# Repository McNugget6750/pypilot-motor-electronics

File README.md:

# pypilot-motor-electronics
Electronics for highly modified pypilot motor in my other repository

I spend the better part of a month to understand and rewrite major parts of the original pypilot motor controller code originally created by seandepagnier moderating the http://forum.openmarine.net/forumdisplay.php?fid=18 forum.

He did an amazing job pulling all these different software packages of OpenPlotter together and creating and maintaining the majority of them as far as I understand. However, the motor controller code needed some work and the controller hardware and h-bridge support needed polishing. I hope I was able to do both.

Design decisions:
* single sided
* hand assembly must be easy
* easy to understand schematics
* support for all sensors and switches originally supported by Sean's code
* additional display for debugging and state information

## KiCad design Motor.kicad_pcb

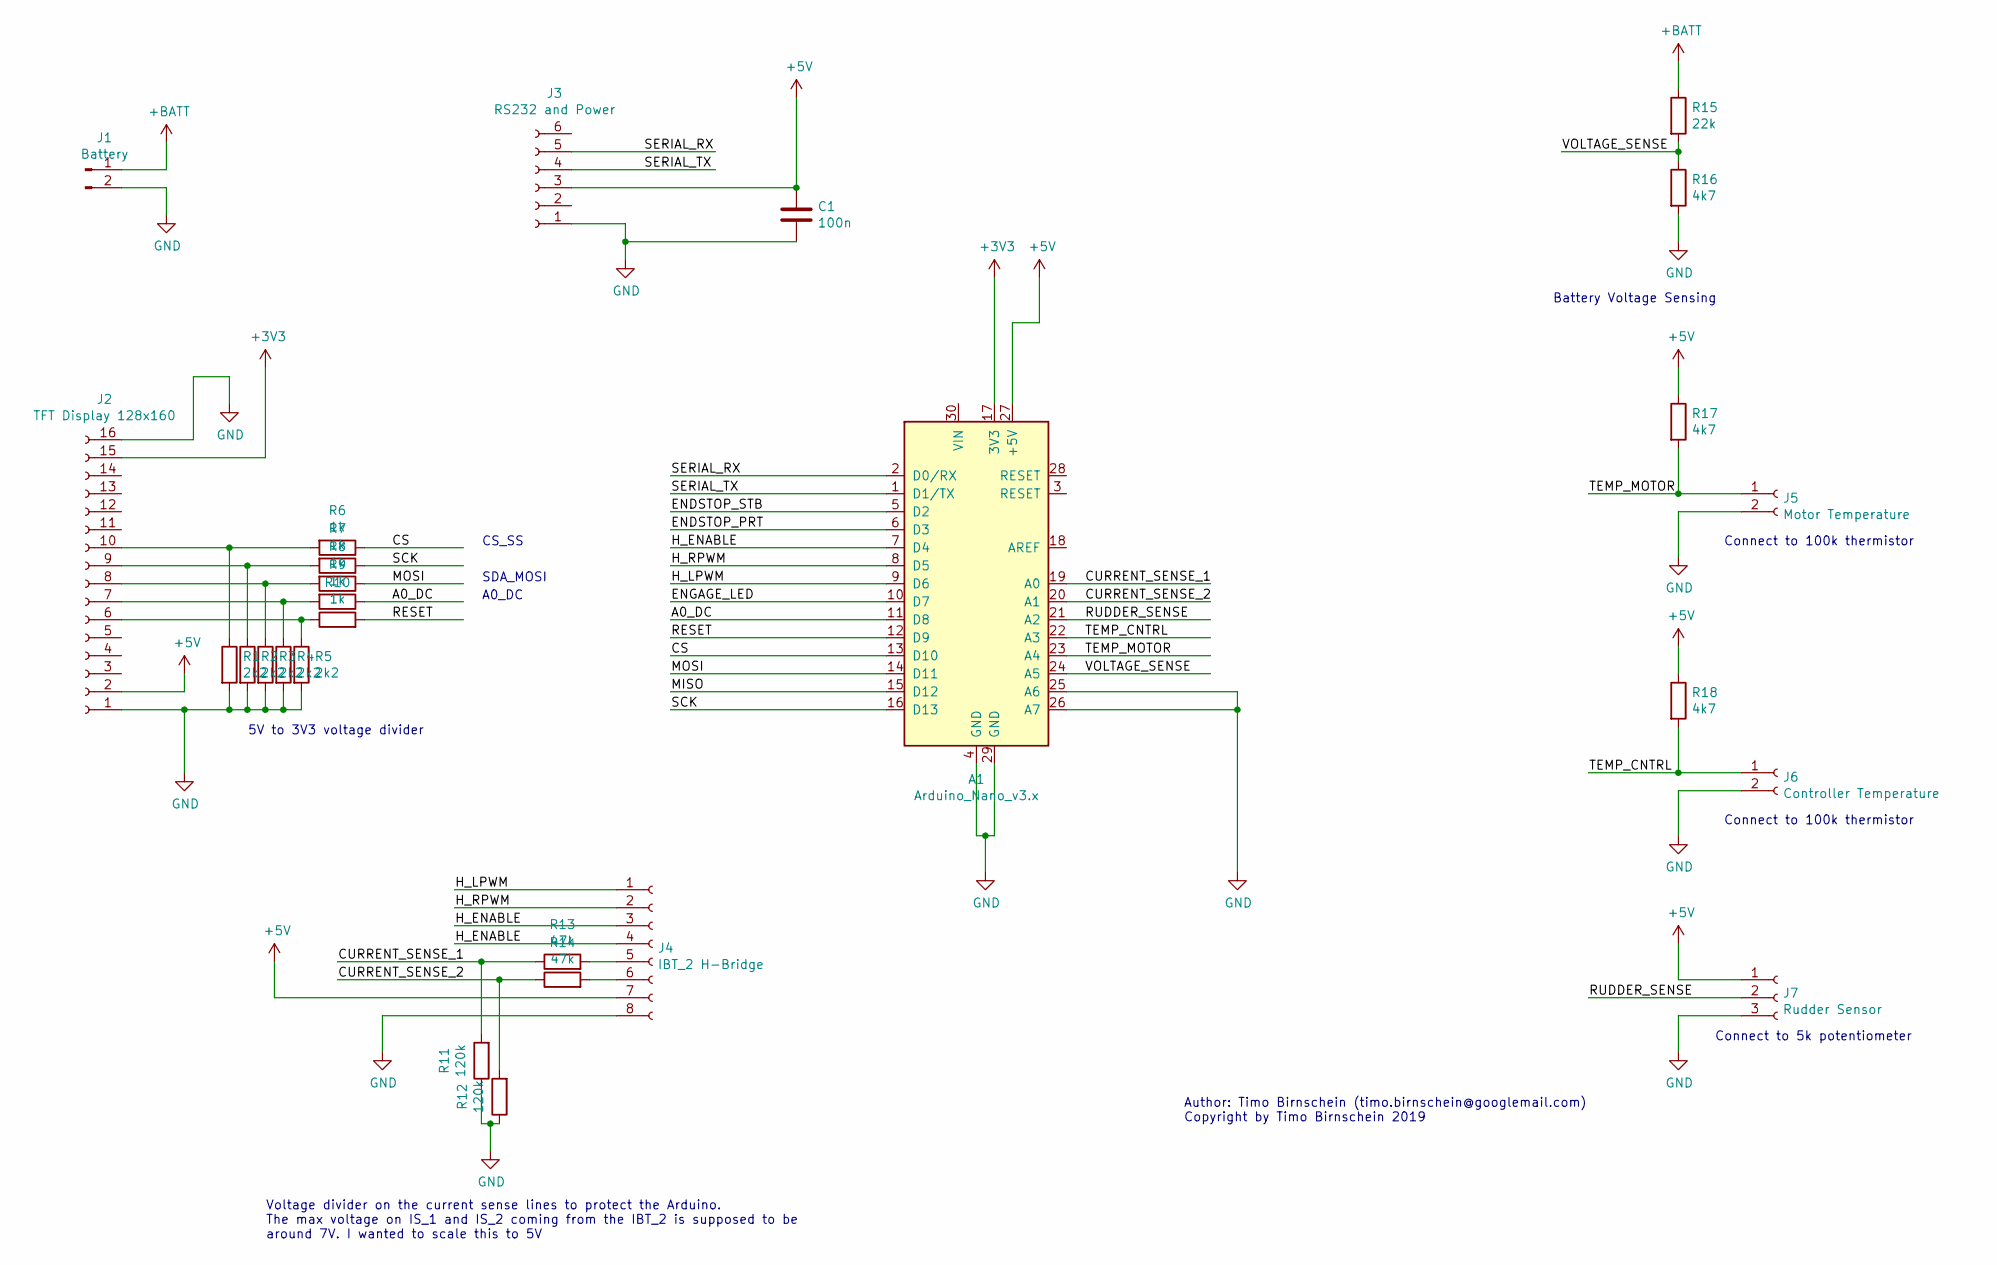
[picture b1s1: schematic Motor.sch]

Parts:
A1: Arduino_Nano_v3.x; Arduino_Nano
C1: 100n; C_0603_1608Metric_Pad1.05x0.95mm_HandSolder
J1: Battery; PinHeader_1x02_P2.54mm_Vertical
J2: TFT Display 128x160; PinHeader_1x16_P2.54mm_Vertical
J3: RS232 and Power; PinHeader_1x06_P2.54mm_Vertical
J4: IBT_2 H-Bridge; PinHeader_1x08_P2.54mm_Vertical
J5: Motor Temperature; PinHeader_1x02_P2.54mm_Vertical
J6: Controller Temperature; PinHeader_1x02_P2.54mm_Vertical
J7: Rudder Sensor; PinHeader_1x03_P2.54mm_Vertical
R1, R2, R3, R4, R5: 2k2; R_Axial_DIN0204_L3.6mm_D1.6mm_P7.62mm_Horizontal
R6, R7, R8, R9, R10: 1k; R_Axial_DIN0204_L3.6mm_D1.6mm_P7.62mm_Horizontal
R11, R12: 120k; R_Axial_DIN0204_L3.6mm_D1.6mm_P7.62mm_Horizontal
R13, R14: 47k; R_Axial_DIN0204_L3.6mm_D1.6mm_P7.62mm_Horizontal
R15: 22k; R_Axial_DIN0204_L3.6mm_D1.6mm_P7.62mm_Horizontal
R16, R17, R18: 4k7; R_Axial_DIN0204_L3.6mm_D1.6mm_P7.62mm_Horizontal

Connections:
+3V3: A1.17 (3V3), J2.15
+5V: A1.27 (+5V), C1.1, J2.2, J3.3, J4.7, J7.1, R17.1, R18.1
+BATT: J1.1, R15.1
/A0_DC: A1.11 (D8), R9.1
/CS: A1.13 (D10), R6.1
/CURRENT_SENSE_1: A1.19 (A0), R11.2, R13.1
/CURRENT_SENSE_2: A1.20 (A1), R12.2, R14.1
/ENDSTOP_PRT: A1.6 (D3)
/ENDSTOP_STB: A1.5 (D2)
/ENGAGE_LED: A1.10 (D7)
/H_ENABLE: A1.7 (D4), J4.3, J4.4
/H_LPWM: A1.9 (D6), J4.1
/H_RPWM: A1.8 (D5), J4.2
/MISO: A1.15 (D12)
/MOSI: A1.14 (D11), R8.1
/RESET: A1.12 (D9), R10.2
/RUDDER_SENSE: A1.21 (A2), J7.2
/SCK: A1.16 (D13), R7.1
/SERIAL_RX: A1.2 (D0/RX), J3.5
/SERIAL_TX: A1.1 (D1/TX), J3.4
/TEMP_CNTRL: A1.22 (A3), J6.1, R18.2
/TEMP_MOTOR: A1.23 (A4), J5.1, R17.2
/VOLTAGE_SENSE: A1.24 (A5), R15.2, R16.1
GND: A1.4 (GND), A1.25 (A6), A1.26 (A7), A1.29 (GND), C1.2, J1.2, J2.1, J2.16, J3.1, J4.8, J5.2, J6.2, J7.3, R1.2, R2.2, R3.2, R4.2, R5.2, R11.1, R12.1, R16.2
unnamed: J2.6, R5.1, R10.1
unnamed: J2.7, R4.1, R9.2
unnamed: J2.8, R3.1, R8.2
unnamed: J2.9, R2.1, R7.2
unnamed: J2.10, R1.1, R6.2
unnamed: J4.5, R13.2
unnamed: J4.6, R14.2

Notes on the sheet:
5V to 3V3 voltage divider
Battery Voltage Sensing
SDA_MOSI
CS_SS
A0_DC
Voltage divider on the current sense lines to protect the Arduino. The max voltage on IS_1 and IS_2 coming from the IBT_2 is supposed to be around 7V. I wanted to scale this to 5V
Connect to 100k thermistor
Connect to 5k potentiometer
Author: Timo Birnschein (timo.birnschein@googlemail.com) Copyright by Timo Birnschein 2019

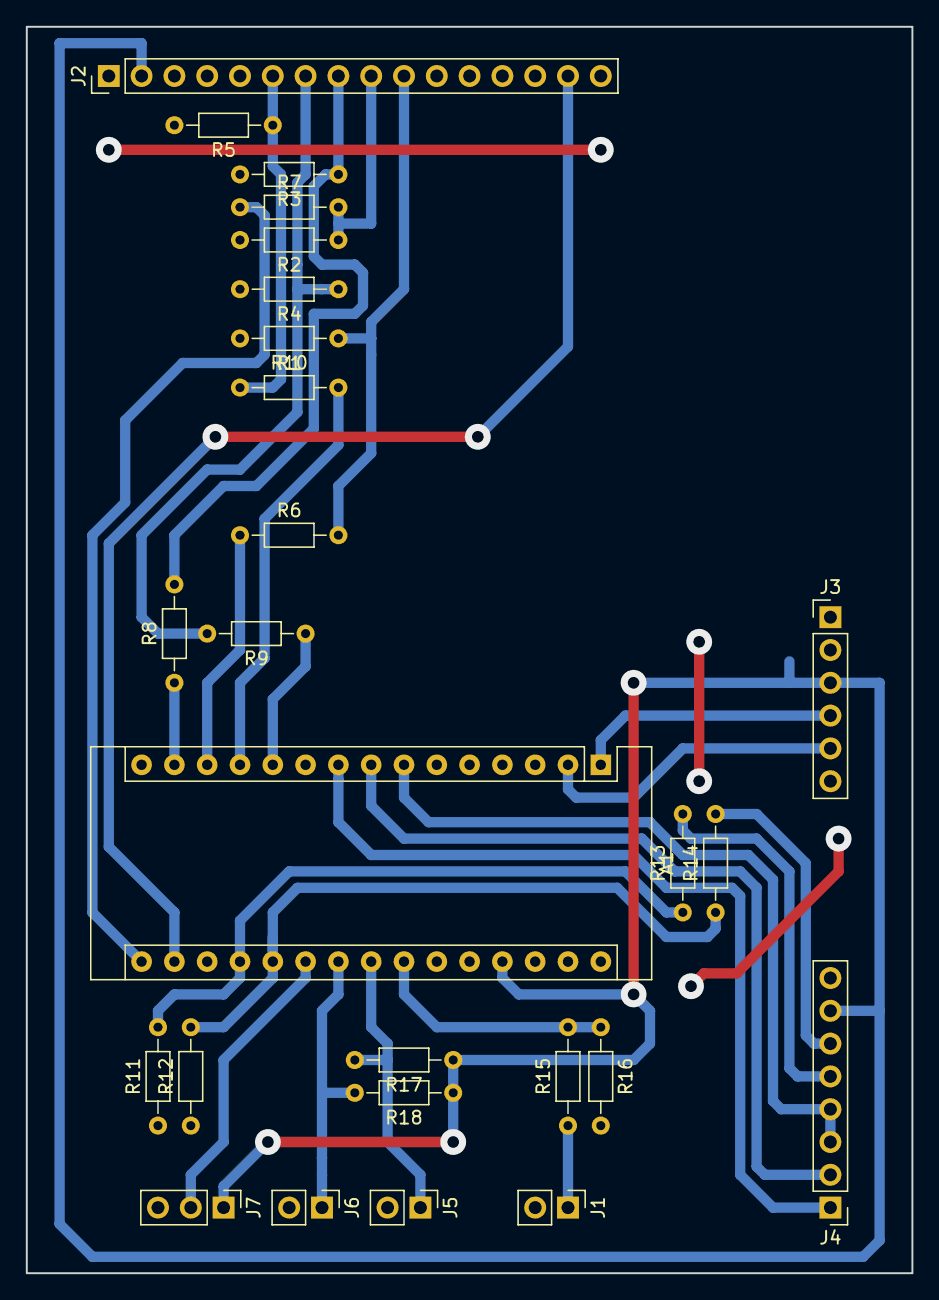
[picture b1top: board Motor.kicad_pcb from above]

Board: 2 copper layers, 68.6 x 96.5 mm, 27 parts (1 on the bottom side), 27 nets.

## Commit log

2019-12-20 Initial commit of pypilot electronics created to work with highly modified pypilot motor controller code in my other repository
2019-12-20 added readme
2019-12-24 added copyright information
2019-12-24 added PDF
2019-12-24 changed license to CC-BY-SA 4
